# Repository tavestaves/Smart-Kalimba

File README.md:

# Smart-Kalimba

CALIBRATION day 1

PREAMPLIFIER CIRCUIT

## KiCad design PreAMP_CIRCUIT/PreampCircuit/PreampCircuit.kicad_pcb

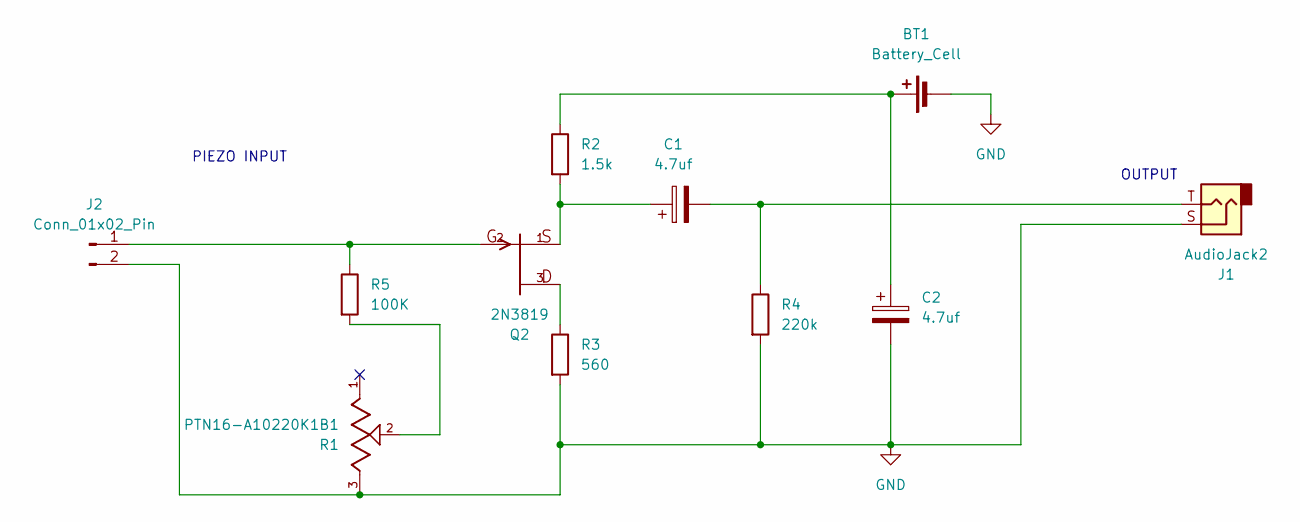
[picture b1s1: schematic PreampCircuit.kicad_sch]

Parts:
BT1: Battery_Cell; 2pads
C1, C2: 4.7uf; CP_Radial_D6.3mm_P2.50mm
J1: AudioJack2; 2pads
J2: Conn_01x02_Pin; 2pads
Q2: 2N3819; JFET; PARTREV June, 2019
R1: PTN16-A10220K1B1; POT_PTN16-A10220K1B1; PARTREV 1.0
R2: 1.5k; R_Axial_DIN0204_L3.6mm_D1.6mm_P7.62mm_Horizontal
R3: 560; R_Axial_DIN0204_L3.6mm_D1.6mm_P7.62mm_Horizontal
R4: 220k; R_Axial_DIN0204_L3.6mm_D1.6mm_P7.62mm_Horizontal
R5: 100K; R_Axial_DIN0204_L3.6mm_D1.6mm_P7.62mm_Horizontal

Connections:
GND: BT1.2 (-), C2.2, J1.S, J2.2, R1.3, R3.2, R4.2
unnamed: BT1.1 (+), C2.1, R2.1
unnamed: C1.1, Q2.1, R2.2
unnamed: C1.2, J1.T, R4.1
unnamed: J2.1, Q2.2, R5.1
unnamed: Q2.3, R3.1
unnamed: R1.2, R5.2

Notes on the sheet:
OUTPUT
PIEZO INPUT

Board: 2 copper layers, 11 parts (0 on the bottom side), 7 nets, no tracks yet.

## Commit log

2025-11-21 init
2025-11-22 Add preamplifier circuit section to README
    Added section for preamplifier circuit with image.
2025-11-22 PREAMP CIRECUIT
    SOURCE: https://www.homemade-circuits.com/diy-contact-mic-circuit/
2025-11-22 PREAMP CIRCUIT
    SOURCE: https://www.homemade-circuits.com/diy-contact-mic-circuit/
2025-12-12 ROUTING
